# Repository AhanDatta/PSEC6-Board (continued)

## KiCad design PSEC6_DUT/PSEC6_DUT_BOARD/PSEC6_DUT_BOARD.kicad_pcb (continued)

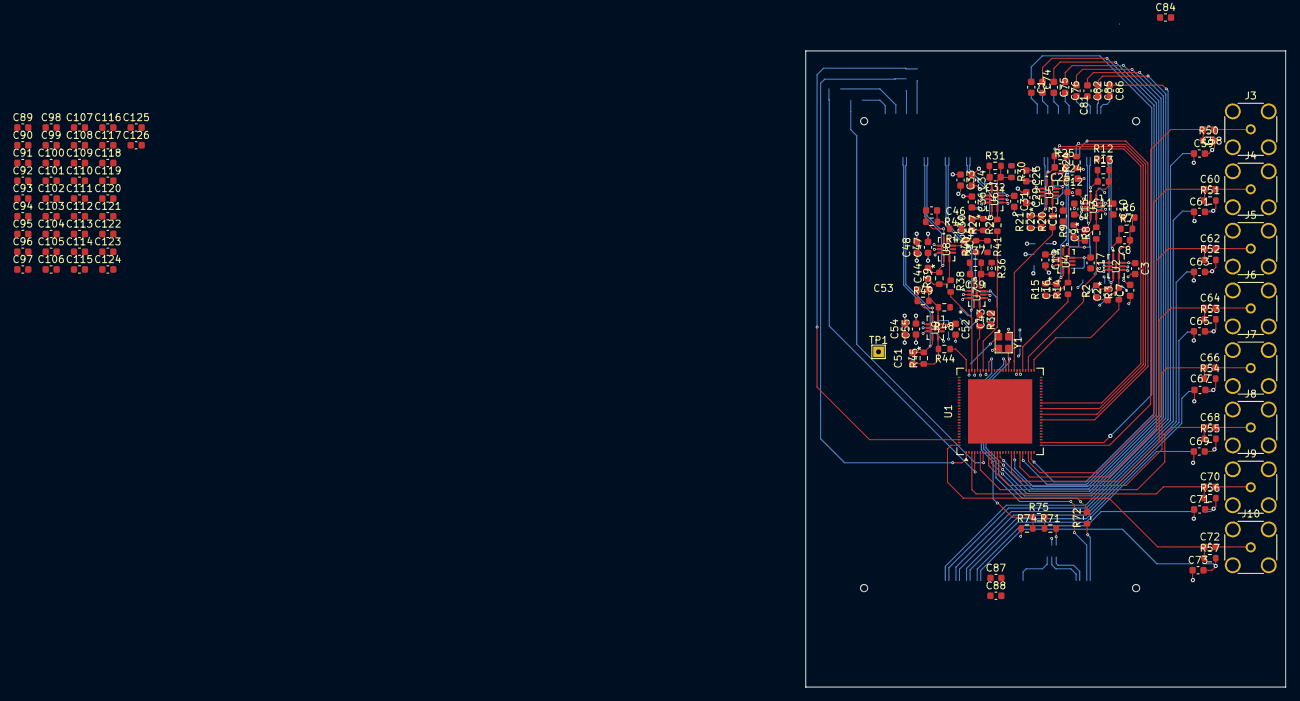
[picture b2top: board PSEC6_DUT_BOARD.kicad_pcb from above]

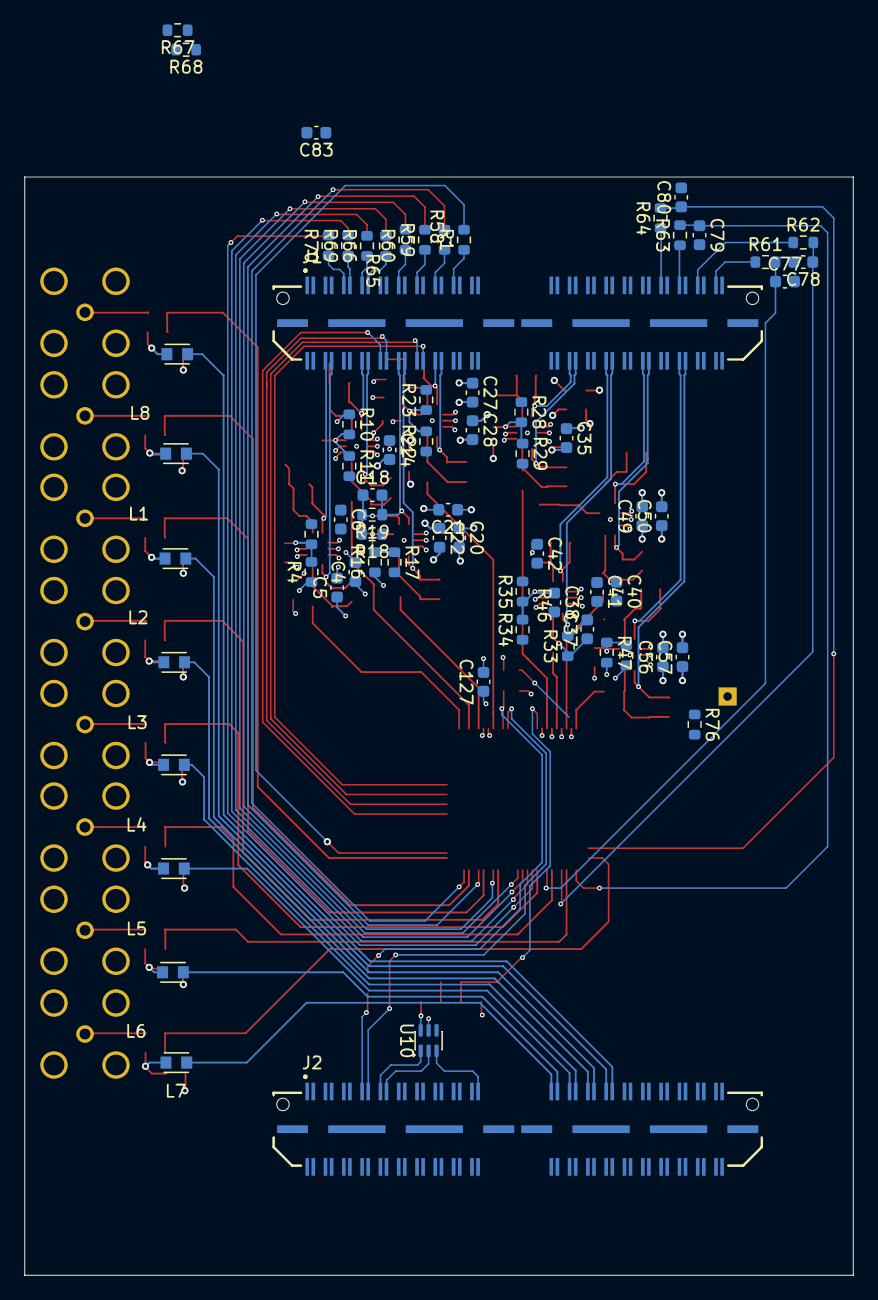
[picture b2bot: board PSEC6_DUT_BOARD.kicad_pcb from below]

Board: 6 copper layers, 67.9 x 90.0 mm, 232 parts (69 on the bottom side), 131 nets.

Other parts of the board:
C1, C74, C75, C76, C77, C78, C79, C80, C81, C82, C83, C84, C85, C86: 330nF; C_0603_1608Metric
C87: 100n; C_0603_1608Metric
C88: 330n; C_0603_1608Metric
R1, R58, R59, R60, R61, R62, R63, R64, R65, R66, R67, R68, R69, R70, R71: 10k; R_0603_1608Metric
U10: DAC8411IDCKT; SOT-363_SC-70-6

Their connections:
/CPIBIAS_RC: C81.1, R65.2; also elsewhere on the board
/DAC_VOUT: C88.2, R71.1; also elsewhere on the board
/DISCBIAS_RC: C86.1, R70.2; also elsewhere on the board
/DIVIBIAS_RC: C82.1, R66.2; also elsewhere on the board
/Disc_Thresh1_RC: C1.1, R1.2; also elsewhere on the board
/Disc_Thresh2_RC: C74.1, R58.2; also elsewhere on the board
/Disc_Thresh3_RC: C75.1, R59.2; also elsewhere on the board
/Disc_Thresh4_RC: C76.1, R60.2; also elsewhere on the board
/Disc_Thresh5_RC: C77.1, R61.2; also elsewhere on the board
/Disc_Thresh6_RC: C78.1, R62.2; also elsewhere on the board
/Disc_Thresh7_RC: C79.1, R63.2; also elsewhere on the board
/Disc_Thresh8_RC: C80.1, R64.2; also elsewhere on the board
/READBIAS1_RC: C83.1, R67.2; also elsewhere on the board
/READBIAS2_RC: C84.1, R68.2; also elsewhere on the board
/WBUFBIAS_RC: C85.1, R69.2; also elsewhere on the board
CPIBIAS: R65.1; also elsewhere on the board
DAC_SCLK: U10.2 (SCLK); also elsewhere on the board
DAC_VIN: U10.3 (DIN); also elsewhere on the board
DISCBIAS: R70.1; also elsewhere on the board
DIVIBIAS: R66.1; also elsewhere on the board
Disc_Thresh1: R1.1; also elsewhere on the board
Disc_Thresh2: R58.1; also elsewhere on the board
Disc_Thresh3: R59.1; also elsewhere on the board
Disc_Thresh4: R60.1; also elsewhere on the board
Disc_Thresh5: R61.1; also elsewhere on the board
Disc_Thresh6: R62.1; also elsewhere on the board
Disc_Thresh7: R63.1; also elsewhere on the board
Disc_Thresh8: R64.1; also elsewhere on the board
GND: C1.2, C74.2, C75.2, C76.2, C77.2, C78.2, C79.2, C80.2, C81.2, C82.2, C83.2, C84.2, C85.2, C86.2, C87.1, C88.1, U10.5 (GND); also elsewhere on the board
unnamed: R71.2, U10.6 (VOUT)
READBIAS1: R67.1; also elsewhere on the board
READBIAS2: R68.1; also elsewhere on the board
SYNC_N: U10.1 (~SYNC); also elsewhere on the board
VDD25: C87.2, U10.4 (AVDD/VREF); also elsewhere on the board
WBUFBIAS: R69.1; also elsewhere on the board
